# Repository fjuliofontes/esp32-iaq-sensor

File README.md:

# ESP32 Indoor-Air-Quality monitor based on BME680

## How to use
Create a Firebase account, flash the firmware, provision the board and you are ready to go.

### Software Required
PlatformIO

### Hardware Required
This example should work with ESP32 based development boards.
You can use the kicad design files to replicate the final design.

### How to build PlatformIO based project

1. [Install PlatformIO Core](http://docs.platformio.org/page/core.html)
2. Download [development platform with examples](https://github.com/platformio/platform-espressif32/archive/develop.zip)
3. Extract ZIP archive
4. Run these commands:

```
# Menu Config
pio run -t menuconfig

# Build project
$ pio run

# Upload firmware to specific port
$ pio run --target upload --upload-port /dev/ttyUSB0

# Build specific environment
$ pio run -e esp32dev

# Upload firmware for the specific environment
$ pio run -e esp32dev --target upload

# Clean build files
$ pio run --target clean
```

### Comments
Power consumption is still under improvement. With a battery of 2000mA the expected lifetime is 70.35 hours (approx 3 days). We've detected peeks of 374.87mA during the transmission that probably can't be improved. However the average of 28.428mA may be.

## Media

### IAQ Board

### IAQ Housing
<p align="center">

</br>
</br>
</br>

</p>

### Dashboard

### Schematics
<p align="center">
</br>

</p>

### Power Consumption
Timestamp in milliseconds (ms).
Current in microampère (µA).
<p align="center">
</br>
</br>

</p>

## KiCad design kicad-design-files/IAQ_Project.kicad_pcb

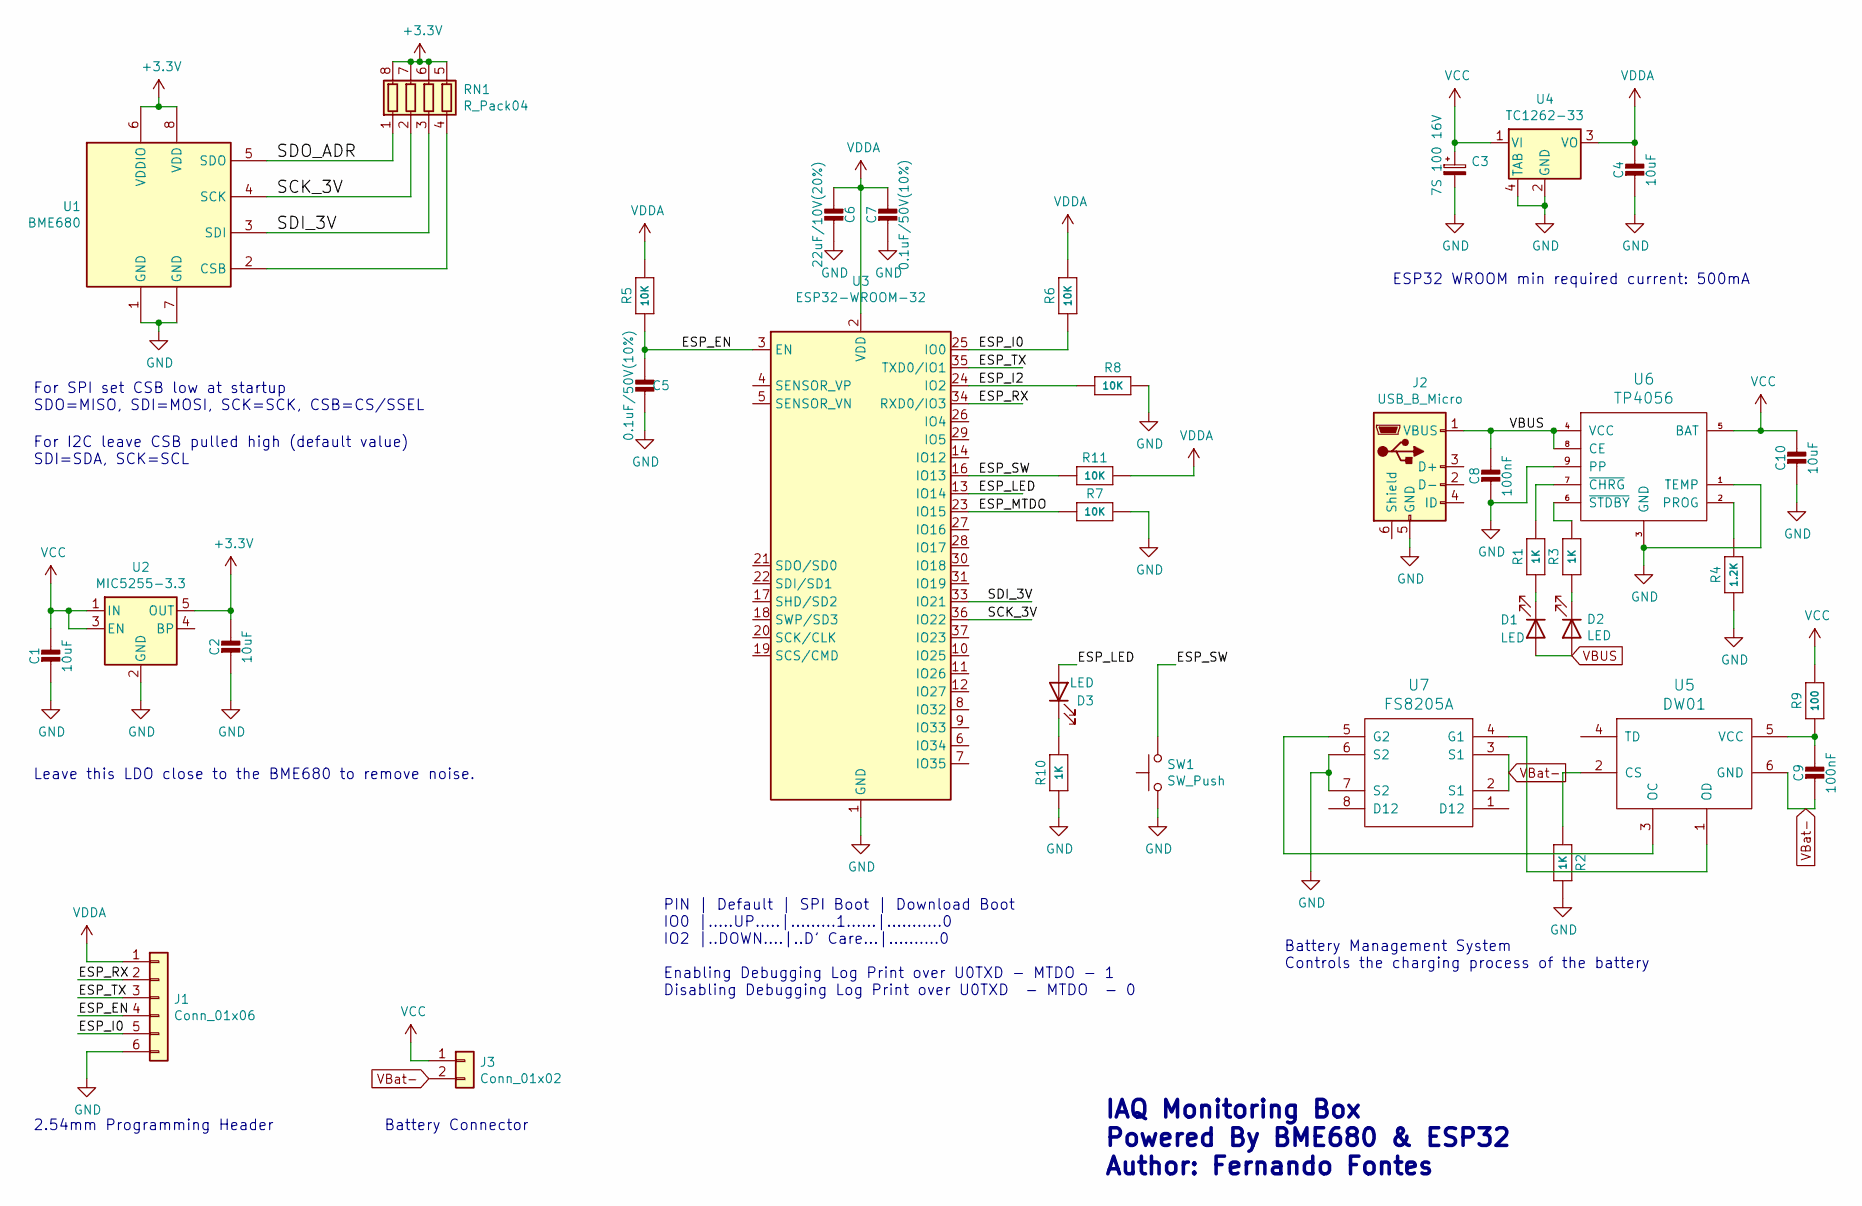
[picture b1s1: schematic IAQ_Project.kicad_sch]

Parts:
C1, C2, C4: 10uF; C_0805_2012Metric
C3: 7S 100 16V; CP_Elec_5x5.9
C5, C7: 0.1uF/50V(10%); C_0805_2012Metric
C6: 22uF/10V(20%); C_0805_2012Metric
C8, C9: 100nF; C_0402_1005Metric
C10: 10uF; C_0504_1310Metric
D1, D2, D3: LED; LED_0805_2012Metric
J1: Conn_01x06; 2.54-programming-header
J2: USB_B_Micro; USB_Micro_SMD_China
J3: Conn_01x02; PinHeader_1x02_P2.00mm_Vertical
R1, R2, R3, R10: 1K; R_0603_1608Metric
R4: 1.2K; R_0603_1608Metric
R5, R6, R7, R8, R11: 10K; R_0603_1608Metric
R9: 100; R_0603_1608Metric
RN1: R_Pack04; R_Array_Convex_4x0603
SW1: SW_Push; SW_SPST_EVQP7C
U1: BME680; Bosch_LGA-8_3x3mm_P0.8mm_ClockwisePinNumbering
U2: MIC5255-3.3; SOT-23-5
U3: ESP32-WROOM-32
U4: TC1262-33; SOT-223
U5: DW01; SOT-23-6
U6: TP4056; TP4056_SOP-8-PP
U7: FS8205A; TSSOP-8_4.4x3mm_P0.65mm

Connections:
+3V3: C2.1, RN1.5 (R4.2), RN1.6 (R3.2), RN1.7 (R2.2), RN1.8 (R1.2), U1.6 (VDDIO), U1.8 (VDD), U2.5 (OUT)
/ESP_EN: C5.2, J1.4, R5.1, U3.3 (EN)
/ESP_I0: J1.5, R6.1, U3.25 (IO0)
/ESP_I2: R8.1, U3.24 (IO2)
/ESP_LED: D3.2 (A), U3.13 (IO14)
/ESP_MTDO: R7.1, U3.23 (IO15)
/ESP_RX: J1.2, U3.34 (RXD0/IO3)
/ESP_SW: R11.1, SW1.2, U3.16 (IO13)
/ESP_TX: J1.3, U3.35 (TXD0/IO1)
/SCK_3V: RN1.2 (R2.1), U1.4 (SCK), U3.36 (IO22)
/SDI_3V: RN1.3 (R3.1), U1.3 (SDI), U3.33 (IO21)
/SDO_ADR: RN1.1 (R1.1), U1.5 (SDO)
GND: C1.2, C2.2, C3.2, C4.2, C5.1, C6.1, C7.2, C8.2, C10.2, J1.6, J2.5 (GND), R2.2, R4.1, R7.2, R8.2, R10.1, SW1.1, U1.1 (GND), U1.7 (GND), U2.2 (GND), U3.1 (GND), U3.15 (GND), U3.38 (GND), U3.39 (GND), U4.2 (GND), U4.4 (TAB), U6.1 (TEMP), U6.3 (GND), U6.9 (PP), U7.6 (S2), U7.7 (S2)
unnamed: C9.1, R9.1, U5.5 (VCC)
unnamed: D1.1 (K), R1.1
unnamed: D2.1 (K), R3.1
unnamed: D3.1 (K), R10.2
unnamed: R1.2, U6.7 (~CHRG)
unnamed: R2.1, U5.2 (CS)
unnamed: R3.2, U6.6 (~STDBY)
unnamed: R4.2, U6.2 (PROG)
unnamed: RN1.4 (R4.1), U1.2 (CSB)
unnamed: U5.1 (OD), U7.4 (G1)
unnamed: U5.3 (OC), U7.5 (G2)
VBUS: C8.1, D1.2 (A), D2.2 (A), J2.1 (VBUS), U6.4 (VCC), U6.8 (CE)
VBat-: C9.2, J3.2, U5.6 (GND), U7.2 (S1), U7.3 (S1)
VCC: C1.1, C3.1, C10.1, J3.1, R9.2, U2.1 (IN), U2.3 (EN), U4.1 (VI), U6.5 (BAT)
VDDA: C4.1, C6.2, C7.1, J1.1, R5.2, R6.2, R11.2, U3.2 (VDD), U4.3 (VO)

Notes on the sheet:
For I2C leave CSB pulled high (default value) SDI=SDA, SCK=SCL
IAQ Monitoring Box Powered By BME680 & ESP32 Author: Fernando Fontes
Battery Connector
Battery Management System Controls the charging process of the battery
ESP32 WROOM min required current: 500mA
Leave this LDO close to the BME680 to remove noise.
2.54mm Programming Header
For SPI set CSB low at startup SDO=MISO, SDI=MOSI, SCK=SCK, CSB=CS/SSEL
PIN | Default | SPI Boot | Download Boot IO0 |.….UP…..|………1……|………..0 IO2 |..DOWN….|..D’ Care…|……….0 Enabling Debugging Log Print over U0TXD - MTDO - 1 Disabling Debugging Log Print over U0TXD - MTDO - 0

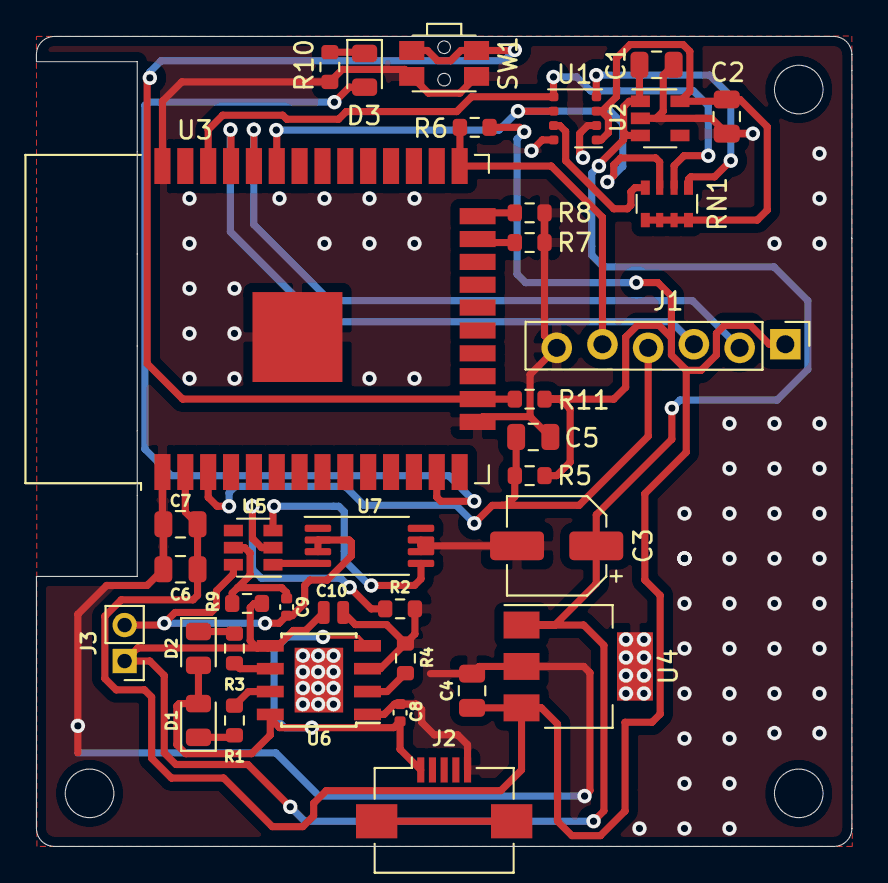
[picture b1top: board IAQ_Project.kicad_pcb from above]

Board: 2 copper layers, 45.3 x 45.0 mm, 36 parts (0 on the bottom side), 28 nets.

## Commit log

2021-12-12 code added
2021-12-12 added kicad design files
2021-12-12 blink when un-provisioned
2021-12-12 led off
2021-12-12 added media
2022-01-16 fixed drifted timestamps
2022-01-30 general fixes
2022-01-30 minor fix
2022-01-30 fix issue that was updating the timestamps for EEPROM readings
2022-02-20 minor fix, media updated
2022-02-20 fixed file type
2022-02-20 renamed ui to ui2
2022-02-20 renamed ui2 to ui
2023-10-21 ported the project to platformio. iram issues
2023-12-18 removed some files
2024-10-27 deep sleep using arduino ide added
2024-12-14 resets provison if button pressed for a while; fix calibration
